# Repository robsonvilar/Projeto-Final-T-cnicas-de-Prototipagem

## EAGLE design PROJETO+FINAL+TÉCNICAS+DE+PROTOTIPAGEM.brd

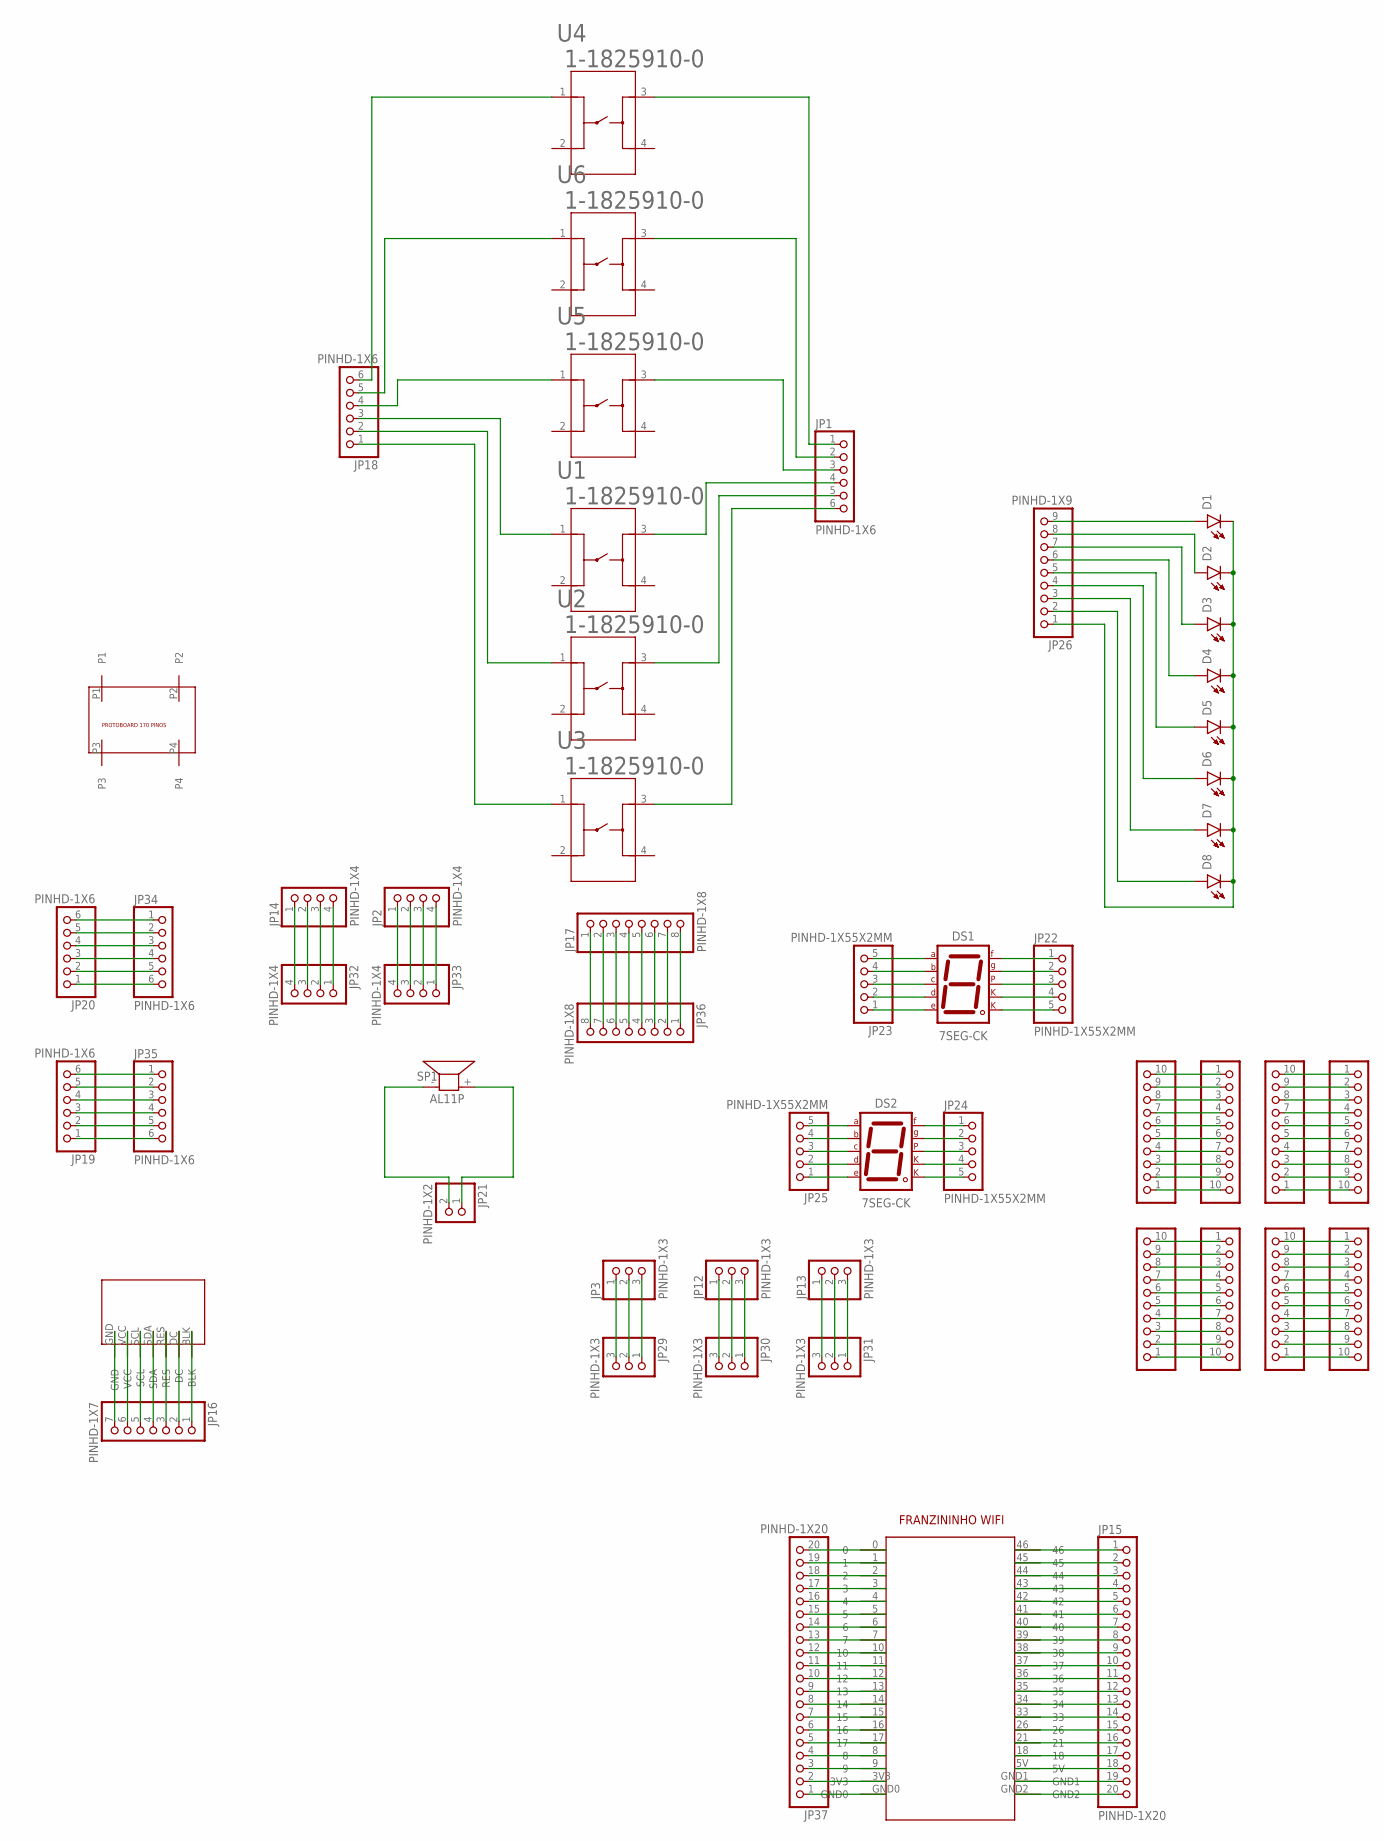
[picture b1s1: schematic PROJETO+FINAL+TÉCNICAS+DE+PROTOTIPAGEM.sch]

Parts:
D1, D2, D3, D4, D5, D6, D7, D8: LED_RADIAL; LEDRD254W60D565H860B_W_V1
DS1, DS2: 7SEG-CK; 7SEG-13
JP1, JP18, JP19, JP20, JP34, JP35: PINHD-1X6; 1X06
JP2, JP14, JP32, JP33: PINHD-1X4; 1X04
JP3, JP12, JP13, JP29, JP30, JP31: PINHD-1X3; 1X03
JP4, JP5, JP6, JP7, JP8, JP9, JP10, JP11: PINHD-1X10; 1X10
JP15, JP37: PINHD-1X20; 1X20
JP16: PINHD-1X7; 1X07
JP17, JP36: PINHD-1X8; 1X08
JP21: PINHD-1X2; 1X02
JP22, JP23, JP24, JP25: PINHD-1X55X2MM; 1_05X2MM
JP26: PINHD-1X9; 1X09
SP1: AL11P
U1, U2, U3, U4, U5, U6: 1-1825910-0; SWITCH_1-1825910-0
U$1: FRANZINO_WIFI; FRANZININHO_WIFI
U$2: DISPLAY_TFT_SPI; PERIMETRO_DISPLAY_TFT
U$3: PROTOBOARD_170_PINOS

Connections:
unnamed: D1.1 (A), JP26.9
unnamed: D2.1 (A), JP26.8
unnamed: D3.1 (A), JP26.7
unnamed: D4.1 (A), JP26.6
unnamed: D5.1 (A), JP26.5
unnamed: D6.1 (A), JP26.4
unnamed: D7.1 (A), JP26.3
unnamed: D8.1 (A), JP26.2
unnamed: D1.2 (C), D2.2 (C), D3.2 (C), D4.2 (C), D5.2 (C), D6.2 (C), D7.2 (C), D8.2 (C), JP26.1
unnamed: JP8.2, JP8.6, JP10.5, JP10.9
unnamed: JP7.2, JP7.6, JP9.5, JP9.9
unnamed: JP4.2, JP4.6, JP6.5, JP6.9
unnamed: JP5.2, JP5.6, JP11.5, JP11.9
unnamed: JP7.1, JP9.10
unnamed: JP7.3, JP9.8
unnamed: JP7.4, JP9.7
unnamed: JP7.5, JP9.6
unnamed: JP1.1, U4.3
unnamed: JP1.2, U6.3
unnamed: JP1.3, U5.3
unnamed: JP1.4, U1.3
unnamed: JP1.5, U2.3
unnamed: JP1.6, U3.3
unnamed: JP18.6, U4.1
unnamed: JP18.5, U6.1
unnamed: JP18.4, U5.1
unnamed: JP18.3, U1.1
unnamed: JP18.2, U2.1
unnamed: JP18.1, U3.1
unnamed: DS1.9 (F), JP22.1
unnamed: DS1.10 (G), JP22.2
unnamed: DS1.5 (DP), JP22.3
unnamed: DS1.3 (CK1), JP22.4
unnamed: DS1.8 (CK2), JP22.5
unnamed: DS1.7 (A), JP23.5
unnamed: DS1.6 (B), JP23.4
unnamed: DS1.4 (C), JP23.3
unnamed: DS1.2 (D), JP23.2
unnamed: DS1.1 (E), JP23.1
unnamed: DS2.9 (F), JP24.1
unnamed: DS2.10 (G), JP24.2
unnamed: DS2.5 (DP), JP24.3
unnamed: DS2.3 (CK1), JP24.4
unnamed: DS2.8 (CK2), JP24.5
unnamed: DS2.7 (A), JP25.5
unnamed: DS2.6 (B), JP25.4
unnamed: DS2.4 (C), JP25.3
unnamed: DS2.2 (D), JP25.2
unnamed: DS2.1 (E), JP25.1
unnamed: JP21.1, SP1.+ (2)
unnamed: JP21.2, SP1.- (1)
unnamed: JP15.11, JP37.16, U$1.4, U$1.36
unnamed: JP15.9, JP37.4, U$1.8, U$1.38
unnamed: JP37.20, U$1.0
unnamed: JP37.19, U$1.1
unnamed: JP37.18, U$1.2
unnamed: JP37.17, U$1.3
unnamed: JP37.15, U$1.5
unnamed: JP37.14, U$1.6
unnamed: JP37.13, U$1.7
unnamed: JP37.12, U$1.10
unnamed: JP37.11, U$1.11
unnamed: JP37.10, U$1.12
unnamed: JP37.9, U$1.13
unnamed: JP37.8, U$1.14
unnamed: JP37.7, U$1.15
unnamed: JP37.6, U$1.16
unnamed: JP37.5, U$1.17
unnamed: JP37.3, U$1.9
unnamed: JP37.2, U$1.3V3
unnamed: JP37.1, U$1.GND0
unnamed: JP15.1, U$1.46
unnamed: JP15.2, U$1.45
unnamed: JP15.3, U$1.44
unnamed: JP15.4, U$1.43
unnamed: JP15.5, U$1.42
unnamed: JP15.6, U$1.41
unnamed: JP15.7, U$1.40
unnamed: JP15.8, U$1.39
unnamed: JP15.10, U$1.37
unnamed: JP15.12, U$1.35
unnamed: JP15.13, U$1.34
unnamed: JP15.14, U$1.33
unnamed: JP15.15, U$1.26
unnamed: JP15.16, U$1.21
unnamed: JP15.17, U$1.18
unnamed: JP15.18, U$1.5V
unnamed: JP15.19, U$1.GND1
unnamed: JP15.20, U$1.GND2
unnamed: JP3.1, JP29.3
unnamed: JP3.2, JP29.2
unnamed: JP3.3, JP29.1
unnamed: JP12.1, JP30.3
unnamed: JP12.2, JP30.2
unnamed: JP12.3, JP30.1
unnamed: JP13.1, JP31.3
unnamed: JP13.2, JP31.2
unnamed: JP13.3, JP31.1
unnamed: JP14.1, JP32.4
unnamed: JP14.2, JP32.3
unnamed: JP14.3, JP32.2
unnamed: JP14.4, JP32.1
unnamed: JP2.1, JP33.4
unnamed: JP2.2, JP33.3
unnamed: JP2.3, JP33.2
unnamed: JP2.4, JP33.1
unnamed: JP20.6, JP34.1
unnamed: JP20.5, JP34.2
unnamed: JP20.4, JP34.3
unnamed: JP20.3, JP34.4
unnamed: JP20.2, JP34.5
unnamed: JP20.1, JP34.6
unnamed: JP19.6, JP35.1
unnamed: JP19.5, JP35.2
unnamed: JP19.4, JP35.3
unnamed: JP19.3, JP35.4
unnamed: JP19.2, JP35.5
unnamed: JP19.1, JP35.6
unnamed: JP17.1, JP36.8
unnamed: JP17.2, JP36.7
unnamed: JP17.3, JP36.6
unnamed: JP17.4, JP36.5
unnamed: JP17.5, JP36.4
unnamed: JP17.6, JP36.3
unnamed: JP17.7, JP36.2
unnamed: JP17.8, JP36.1
unnamed: JP7.7, JP9.4
unnamed: JP7.8, JP9.3
unnamed: JP7.9, JP9.2
unnamed: JP7.10, JP9.1
unnamed: JP8.1, JP10.10
unnamed: JP8.3, JP10.8
unnamed: JP8.4, JP10.7
unnamed: JP8.5, JP10.6
unnamed: JP8.7, JP10.4
unnamed: JP8.8, JP10.3
unnamed: JP8.9, JP10.2
unnamed: JP8.10, JP10.1
unnamed: JP4.1, JP6.10
unnamed: JP4.3, JP6.8
unnamed: JP4.4, JP6.7
unnamed: JP4.5, JP6.6
unnamed: JP4.7, JP6.4
unnamed: JP4.8, JP6.3
unnamed: JP4.9, JP6.2
unnamed: JP4.10, JP6.1
unnamed: JP5.1, JP11.10
unnamed: JP5.3, JP11.8
unnamed: JP5.4, JP11.7
unnamed: JP5.5, JP11.6
unnamed: JP5.7, JP11.4
unnamed: JP5.8, JP11.3
unnamed: JP5.9, JP11.2
unnamed: JP5.10, JP11.1
unnamed: JP16.7, U$2.GND
unnamed: JP16.6, U$2.VCC
unnamed: JP16.5, U$2.SCL
unnamed: JP16.4, U$2.SDA
unnamed: JP16.3, U$2.RES
unnamed: JP16.2, U$2.DC
unnamed: JP16.1, U$2.BLK

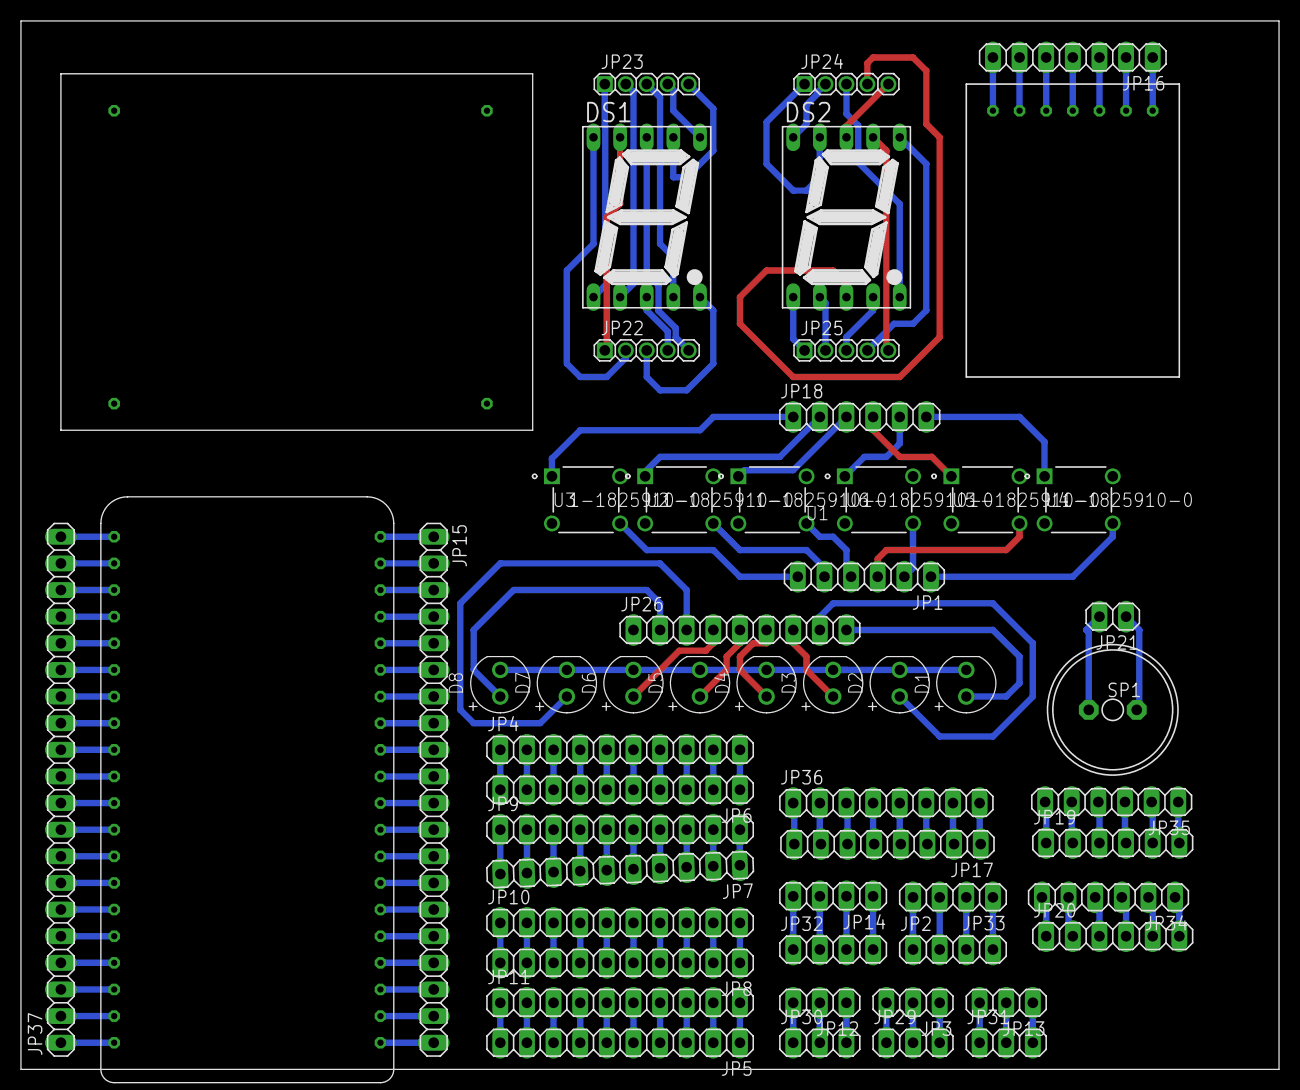
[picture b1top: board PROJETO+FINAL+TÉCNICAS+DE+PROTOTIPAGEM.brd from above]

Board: 2 copper layers, 120.0 x 100.0 mm, 55 parts (0 on the bottom side), 161 nets.

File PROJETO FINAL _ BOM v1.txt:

Partlist exported from C:/Users/Caique/AppData/Local/Temp/Neutron/ElectronFileOutput/10580/sch-1ef48dca-40aa-4480-90f6-bb926bfd932a/PROJETO FINAL TÉCNICAS DE PROTOTIPAGEM v1.sch at 21/12/2022 13:40

Qty Value                Device               Package                   Parts                                    Description              BUILT_BY    CATEGORY         COPYRIGHT                                                   DESCRIPTION                       MANUFACTURER MANUFACTURER_PART_NUMBER MF MPN OC_FARNELL OC_NEWARK OPERATING_TEMP PART_STATUS POPULARITY ROHS_COMPLIANT SERIES  SUB-CATEGORY THERMALLOSS TYPE      VENDOR         
8                        LED_RADIAL           LEDRD254W60D565H860B_W_V1 D1, D2, D3, D4, D5, D6, D7, D8           LED - Generic                                                                                                                                                                                                                                                                                                                        
6   1-1825910-0          1-1825910-0          SWITCH_1-1825910-0        U1, U2, U3, U4, U5, U6                                            EMA_UL_Team Tactile Switches Copyright (C) 2016 Accelerated Designs. All rights reserved FSM6JH=6MM TACT SWITCH, HIGH TEMP              1-1825910-0                                                         active                                Unknown                                    TE Connectivity
2   7SEG-CK              7SEG-CK              7SEG-13                   DS1, DS2                                 7-segment DISPLAY                    Opto-Electronic                                                                                                                                                                                                                               Display                  7-Segment                
1   AL11P                AL11P                AL11P                     SP1                                      SPEAKER Source: Buerklin                                                                                                                                                                         unknown    unknown                              3                                                                                   
1   DISPLAY_TFT_SPI      DISPLAY_TFT_SPI      PERIMETRO_DISPLAY_TFT     U$2                                                                                                                                                                                                                                                                                                                                                                           
1   FRANZINO_WIFI        FRANZINO_WIFI        FRANZININHO_WIFI          U$1                                                                                                                                                                                                                                                                                                                                                                           
8   PINHD-1X10           PINHD-1X10           1X10                      JP4, JP5, JP6, JP7, JP8, JP9, JP10, JP11 PIN HEADER                           CONNECTOR                                                                                                                                                                                                                                     PIN-HEADER                                        
1   PINHD-1X2            PINHD-1X2            1X02                      JP21                                     PIN HEADER                           CONNECTOR                                                                                                                                                                                                                                     PIN-HEADER                                        
2   PINHD-1X20           PINHD-1X20           1X20                      JP15, JP37                               PIN HEADER                           CONNECTOR                                                                                                                                                                                                                                     PIN-HEADER                                        
6   PINHD-1X3            PINHD-1X3            1X03                      JP3, JP12, JP13, JP29, JP30, JP31        PIN HEADER                           CONNECTOR                                                                                                                                                                                                                                     PIN-HEADER                                        
4   PINHD-1X4            PINHD-1X4            1X04                      JP2, JP14, JP32, JP33                    PIN HEADER                           CONNECTOR                                                                                                                                                                                                                                     PIN-HEADER                                        
4   PINHD-1X55X2MM       PINHD-1X55X2MM       1_05X2MM                  JP22, JP23, JP24, JP25                   PIN HEADER                           CONNECTOR                                                                                                                                                                                                                                     PIN-HEADER                                        
6   PINHD-1X6            PINHD-1X6            1X06                      JP1, JP18, JP19, JP20, JP34, JP35        PIN HEADER                           CONNECTOR                                                                                                                                                                                                                                     PIN-HEADER                                        
1   PINHD-1X7            PINHD-1X7            1X07                      JP16                                     PIN HEADER                           CONNECTOR                                                                                                                                                                                                                                     PIN-HEADER                                        
2   PINHD-1X8            PINHD-1X8            1X08                      JP17, JP36                               PIN HEADER                           CONNECTOR                                                                                                                                                                                                                                     PIN-HEADER                                        
1   PINHD-1X9            PINHD-1X9            1X09                      JP26                                     PIN HEADER                           CONNECTOR                                                                                                                                                                                                                                     PIN-HEADER                                        
1   PROTOBOARD_170_PINOS PROTOBOARD_170_PINOS PROTOBOARD_170_PINOS      U$3

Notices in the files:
parts and their libraries:
COPYRIGHT: Copyright (C) 2016 Accelerated Designs. All rights reserved
